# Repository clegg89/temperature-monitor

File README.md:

# Temperature Monitoring Application

This application is used to remotely monitor a temperature sensor via MQTT.

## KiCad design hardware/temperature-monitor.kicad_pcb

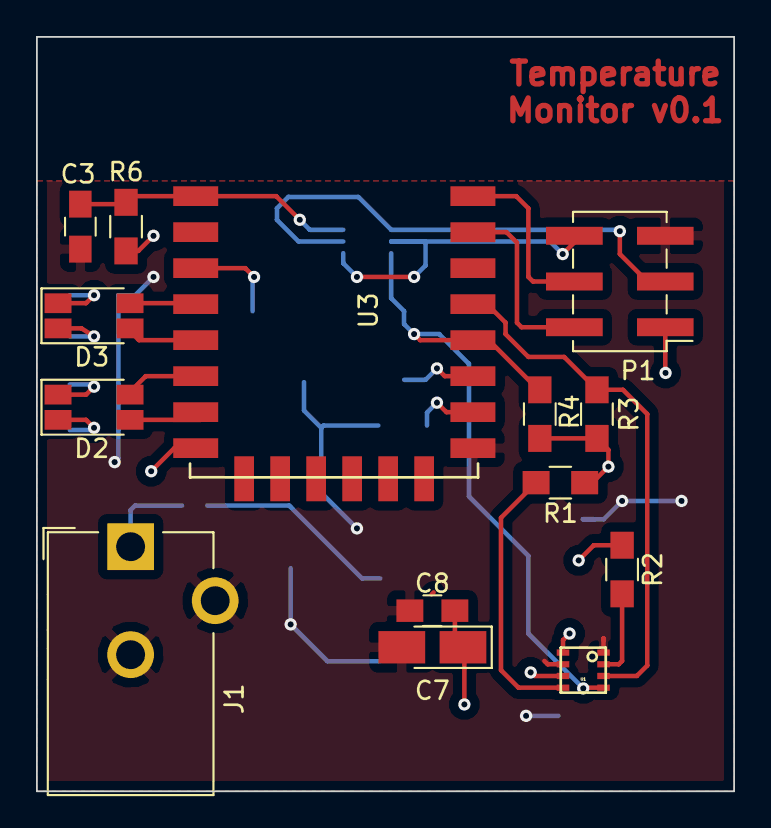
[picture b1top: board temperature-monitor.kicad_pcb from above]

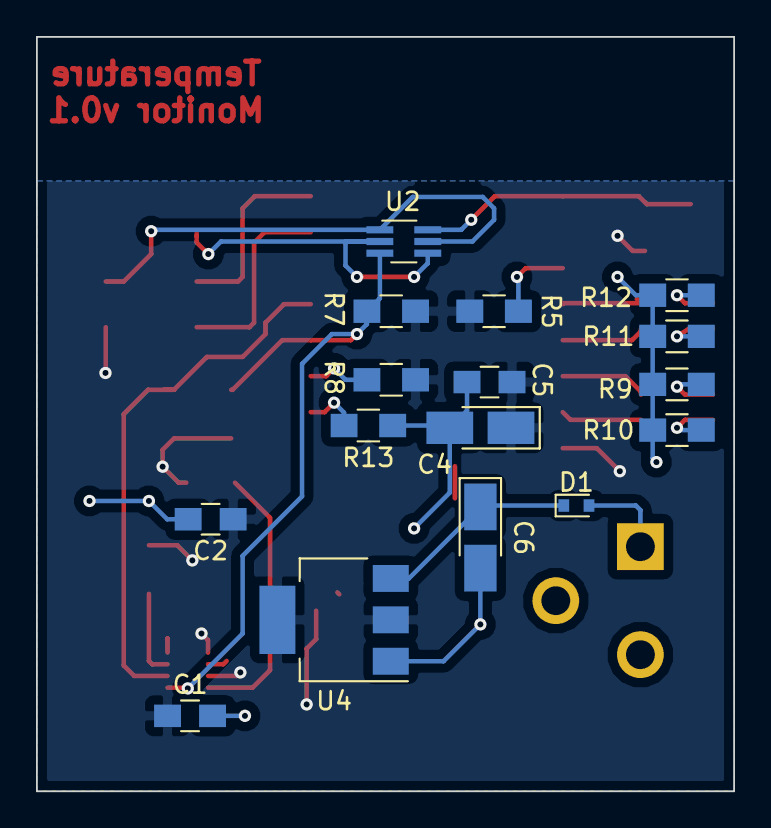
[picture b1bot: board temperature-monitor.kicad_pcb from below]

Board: 2 copper layers, 38.7 x 41.9 mm, 30 parts (16 on the bottom side), 24 nets.

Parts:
C1, C2, C3, C5, C8: 0.1uF; C_0805_HandSoldering
C4, C6, C7: 10uF; CP_Tantalum_Case-R_EIA-2012-12_Hand
D1: D; D_SOD-523
D2, D3: LED_Dual_ACAC; HSMF-C15x
J1: PJ-102AH; Barrel_Jack_CUI_PJ-102AH
P1: CONN_02X03; Pin_Header_Straight_2x03_Pitch2.54mm_SMD
R1, R2, R3, R4: 4.7K; R_0805_HandSoldering
R5, R6, R7, R8, R13: 12K; R_0805_HandSoldering
R9, R10, R11, R12: R; R_0805_HandSoldering
U1: BME280
U2: UMH3N; SOT-363_SC-70-6_Handsoldering
U3: ESP-12F; ESP-12E_SMD
U4: LM1117-3.3; SOT-223-3_TabPin2

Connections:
+3V3: C1.1, C2.1, C4.1, C5.1, C7.1, C8.1, P1.1, R1.1, R2.1, R3.1, R4.1, R5.2, R6.2, R7.2, R8.2, U1.6, U1.8, U3.8, U4.2
/DTR: P1.6, U2.2, U2.4
/EN: R5.1, U3.3
/GPIO0: R4.2, R7.1, U1.4, U2.3, U3.18
/GPIO2: R8.1, U3.17
/PWRIN: D1.2, J1.1
/RST: C3.1, R6.1, U2.6, U3.1
/RTS: P1.3, U2.1, U2.5
/RX: P1.2, U3.21
/SDA: R3.2, U1.3, U3.19
/TX: P1.4, U3.22
GND: C1.2, C2.2, C3.2, C4.2, C5.2, C6.2, C7.2, C8.2, J1.2, J1.3, P1.5, R9.2, R10.2, R11.2, R12.2, R13.2, U1.1, U1.7, U3.15, U4.1
unnamed: C6.1, D1.1, U4.3
unnamed: D2.1, U3.7
unnamed: D2.2, R10.1
unnamed: D2.3, U3.6
unnamed: D2.4, R9.1
unnamed: D3.1, U3.5
unnamed: D3.2, R11.1
unnamed: D3.3, U3.4
unnamed: D3.4, R12.1
unnamed: R1.2, U1.5
unnamed: R2.2, U1.2
unnamed: R13.1, U3.16

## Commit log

2017-08-05 Initial Commit. Node directory setup with platformio
2017-08-05 Added defaults and libraries to platformio.ini
2017-08-05 Added initial main source file
2017-08-05 Added ArduinoMqtt library to platformio.ini
2017-08-06 Fleshed out first part of main. Added tool to generate WiFi information
2017-08-06 Added DHT initialization code
2017-08-06 Modified wifi-setup to place files directly in source instead of library
2017-08-07 Added support for TLS connection using CA Certificate verification.
    Currently certificate verification is not working. This step required
    switching to the staged version of the ESP8266 Arduino Framework, as
    only the latest Arduino Core has support for CA Certificates. Details
    on how to do this can be found at:
    http://docs.platformio.org/en/latest/platforms/espressif8266.html#using-arduino-framework-with-staging-version
2017-08-12 SSL working
    The changes were mostly outside of the code committed to the repository:
    - Needed to use most up-to-date ESP8266 Arduino Core
    - Use Root CA instead of intermediate CA
    Added some documentation and the ability to turn on Core debugging.
2017-08-12 Moved Root CA to a vector, created wrapper around WiFiClientSecure
2017-08-18 Added Tasking Library. Moved all logic into specific tasks
2017-08-18 Added logic to poll temperture sensor to task
2017-08-19 First pass at network queue to allow sensor task to send messages
2017-08-19 Added ETL
2017-08-19 Remove Embedded Template Library (naming conflict)
2017-08-19 Implement network queue
2017-08-26 Added network messaging task and surrounding infrastructure.
    Modified Wifi Information. Added Security Information and MQTT Broker Information.
    Added tool to generate MQTT Broker information.
2017-08-26 Added tool to generate keys
2017-08-26 Removed print of password for WiFi
2017-08-26 Increase keepalive interval, other small changes
2017-08-27 Moved Security Generator to top level. Now generates for both host and node
2017-08-27 Moved MQTT setup script to top directory, now handles node and host usernames
2017-08-27 Added initial host application
2017-08-27 Removed Null terminator on message
2017-08-27 Working host application. Receives messages over MQTT and correctly unencrypts, verifies and displays information
2017-09-04 Added KiCad project
2017-09-04 Added relevant datasheets
2017-09-04 Changed directory names to be more descriptive
2017-09-17 Changed functions to static
2017-09-17 Added commented debug option
2017-09-17 Added InfluxDB integration, including credential generation script
2017-09-23 Removed DHT library, installed BME280 library
2017-09-23 Changed code to use BME280 instead of DHT, untested
2017-09-24 Fix to construction of MqttClient
2017-09-24 Some bug fixes
2017-09-24 Another small fix
2017-10-01 Begin to work on some of the schematic
2017-10-01 Added relevant documents for ESP8266
2017-10-01 More work on schematic. Need to add power.
2017-10-02 Added power connector
2017-10-07 Created new symbol for barrel jack. Added LDO (LM1117). Add LDO datasheet.
2017-10-07 Added barrel jack datasheet
2017-10-16 Explicitly convert values to floats
2017-10-17 Added LEDs to schematic
2017-10-17 Added LED datasheet
2017-10-30 Some fixes to schematic. Finished layout
2017-10-30 Generated Gerbers
